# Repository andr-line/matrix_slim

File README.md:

# Matrix Slim

> Attention: This keyboard is in developement and the pcb is not yet functional.
> 
> The description below describes a future version of the keyboard, at the moment it is the circuitry of a nice!nano and the antenna matching circuit is not functional yet.

> The project is currently on hold so I can focus on Uni, at least until summer 2025.

This is the successor to my original Matrix keyboard, which was far from perfect. It aims to be as compact as possible while still providing enough keys to not have to re-learn to type. Using the new surface mounted kailh CPG1316M01D02 and the corresponding slim CPG1316S01D02 switches the size was able to be reduced to just [INSERT SIZE HERE] cm by [INSERT THICKNESS HERE] mm. This version also introduces column stagger for more comfort, especially for the little finger.

## Design remarks
Since stacking controller (nice!nano or seeduino) and battery vertically would increase the thickness, I decided to implement the seeduino xiao ble directly in the pcb (by copying their design). This results in the circuitry being very compact and allows for the addition of a e-ink display on top of the battery. (Alternatively more keys or different accessories could be added). Note that this is my first pcb with a microchip and there could be errors / bad design.

## Incomplete:

- [ ] New iteration using copied seeduino xiao ble instead of nice!nano
- [ ] Use NRF52840-CKAA-R footprint for compactness
- [ ] Use new free space for battery and maybe display (Chip should be entirely in old thumbcluster)

## Potential additions:

- [ ] Display
- [ ] Trackpoint

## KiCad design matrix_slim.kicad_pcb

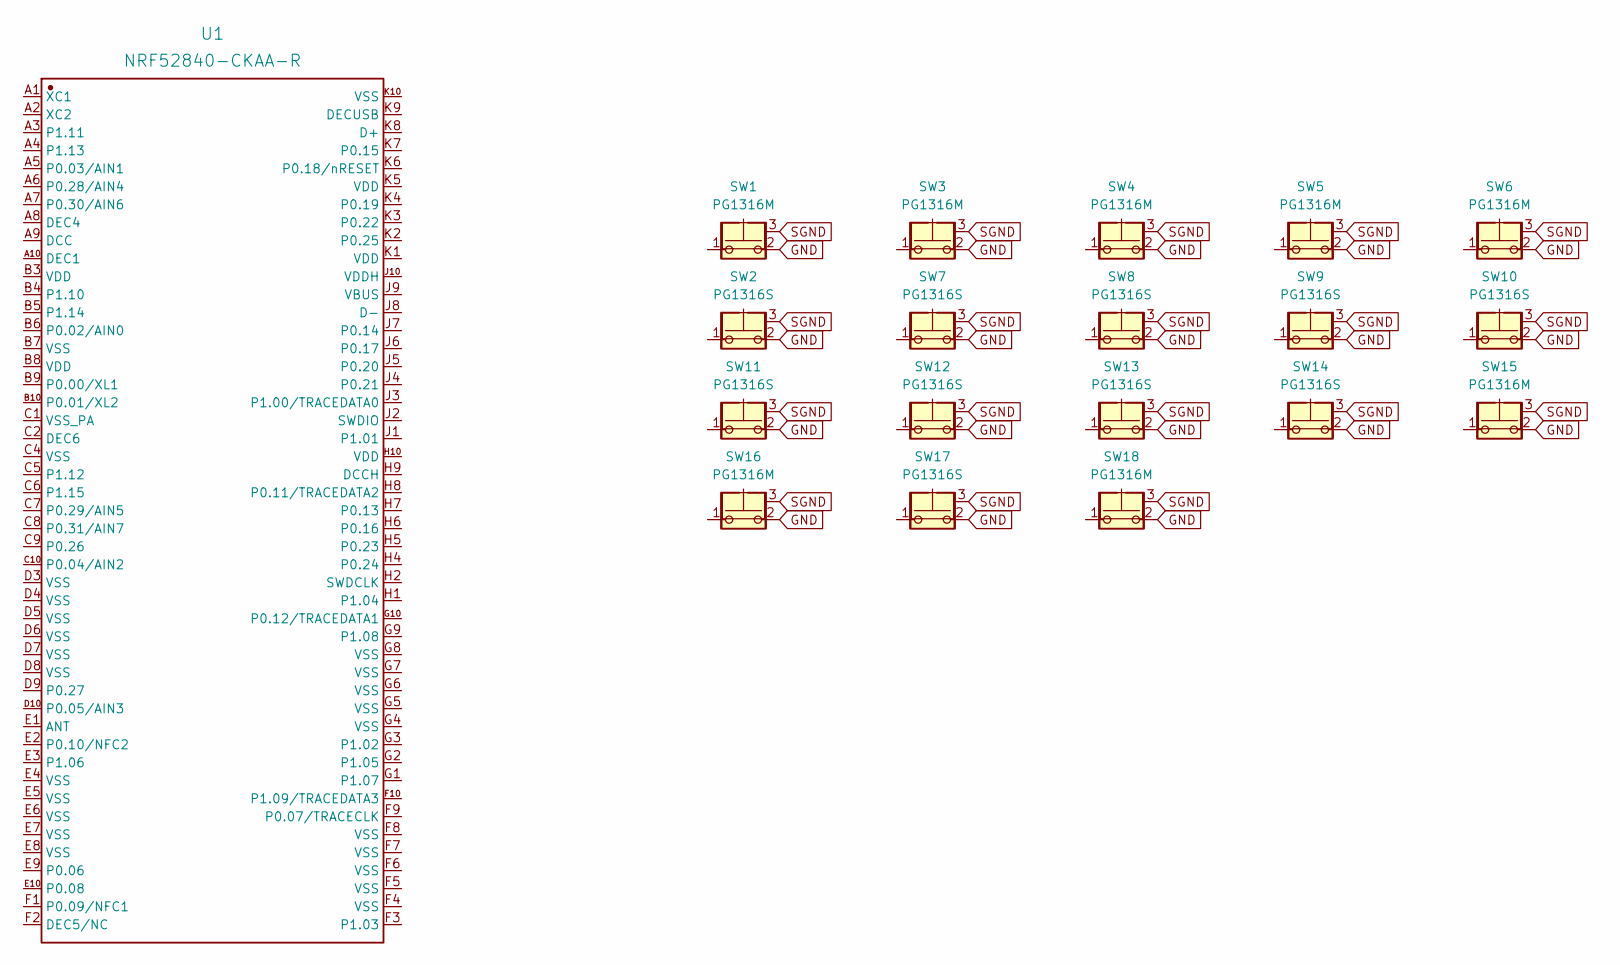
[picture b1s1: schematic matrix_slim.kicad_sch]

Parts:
SW1, SW3, SW4, SW5, SW6, SW15, SW16, SW18: PG1316M
SW2, SW7, SW8, SW9, SW10, SW11, SW12, SW13, SW14, SW17: PG1316S
U1: NRF52840-CKAA-R; Manufacturer Part NRF52840-CKAA-R

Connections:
GND: SW1.2, SW2.2, SW3.2, SW4.2, SW5.2, SW6.2, SW7.2, SW8.2, SW9.2, SW10.2, SW11.2, SW12.2, SW13.2, SW14.2, SW15.2, SW16.2, SW17.2, SW18.2
SGND: SW1.3 (SGND), SW2.3 (SGND), SW3.3 (SGND), SW4.3 (SGND), SW5.3 (SGND), SW6.3 (SGND), SW7.3 (SGND), SW8.3 (SGND), SW9.3 (SGND), SW10.3 (SGND), SW11.3 (SGND), SW12.3 (SGND), SW13.3 (SGND), SW14.3 (SGND), SW15.3 (SGND), SW16.3 (SGND), SW17.3 (SGND), SW18.3 (SGND)

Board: 2 copper layers, 19 parts (0 on the bottom side), 2 nets, no tracks yet.

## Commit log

2024-11-12 Added gitignore clientside
2024-11-12 Revert "Added gitignore clientside"
    This reverts commit 4a7f1266c80ddde484a848c1a033347ce4ddd6a8.
2024-11-12 Deleted DS_Store
2025-01-03 Added base setup
